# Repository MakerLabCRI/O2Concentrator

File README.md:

# O2Concentrator
# Designed by Youssouph Ndao

- Shield to connect Medical O2 sensors and valves to Movuino ESP32 for making frugal o2 O2Concentrator

- Breakout for pressure sensors

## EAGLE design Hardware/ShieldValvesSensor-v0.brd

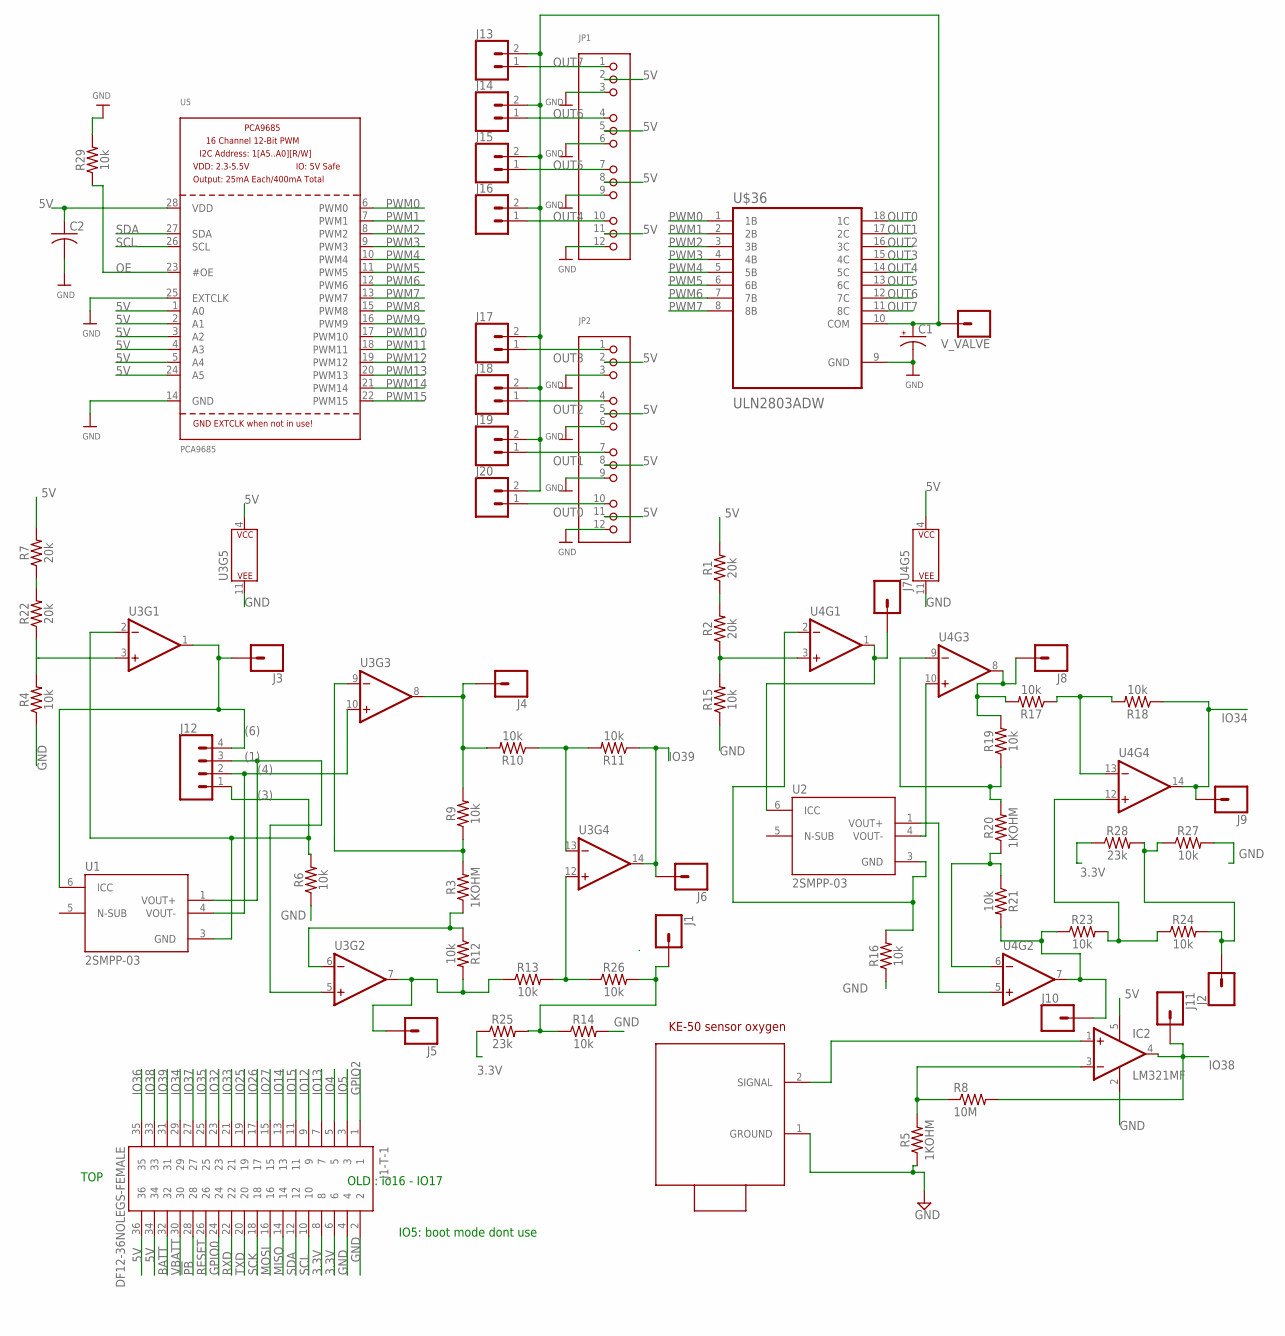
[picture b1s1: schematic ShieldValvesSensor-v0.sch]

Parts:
C1: CPOL-USE2-4; E2-4
C2: C-USC0402; C0402
IC2: LM321MF; SOT23-5
J1, J2, J3, J4, J5, J6, J7, J8, J9, J10, J11: CONN_01; 1X01
J1-T-1: DF12-36NOLEGS-FEMALE; DF12-36-DP-NL
J12: CONN_04PTH; 1X04
J13, J14, J15, J16, J17, J18, J19, J20: CONN_02; 1X02
JP1, JP2: HEADER-3X04; 3X04
R1, R2, R7, R22: 20k; 0402-TIGHT
R3, R5, R20: 1KOHM; 0402
R4, R6, R9, R10, R11, R12, R13, R14, R15, R16, R17, R18, R19, R21, R23, R24, R26, R27, R29: 10k; 0402
R8: 10M; R0402
R25, R28: 23k; 0402-TIGHT
U1, U2: 2SMPP-03; XDCR_2SMPP-03
U3, U4: LMV324SOP127P780X200-14N; SOP127P780X200-14N
U5: PCA9685; TSSOP28
U$5: KE-50; KE
U$36: ULN2803ADW; SOIC127P1030X265-18N
V_VALVE: CONN_01; 1X01

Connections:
3.3V: J1-T-1.6, J1-T-1.8, R25.1, R28.1
5V: C2.1, IC2.5 (V+), J1-T-1.34, J1-T-1.36, JP1.2, JP1.5, JP1.8, JP1.11, JP2.2, JP2.5, JP2.8, JP2.11, R1.2, R7.2, U3.4 (P$V+), U4.4 (P$V+), U5.1 (A0), U5.2 (A1), U5.3 (A2), U5.4 (A3), U5.5 (A4), U5.24 (A5), U5.28 (VDD)
!PB!: J1-T-1.28
(1): J12.3, U1.1 (VOUT+), U3.5 (+IN)
(3): J12.1, R6.2, U1.3 (GND), U3.2 (-IN)
(4): J12.2, U1.4 (VOUT-), U3.10 (+IN)
(6): J3.1, J12.4, U1.6 (ICC), U3.1 (OUT)
+IND2: R2.1, R15.2
-INA: R10.1, R11.2
-INC2: R19.1, R20.2, U4.9 (-IN)
-IND2: R16.2, U2.3 (GND), U4.2 (-IN)
BATT: J1-T-1.32
GND: C1.-, C2.2, IC2.2 (V-), J1-T-1.2, J1-T-1.4, JP1.3, JP1.6, JP1.9, JP1.12, JP2.3, JP2.6, JP2.9, JP2.12, R4.1, R5.1, R6.1, R14.2, R15.1, R16.1, R27.2, R29.2, U3.11 (P$V-), U4.11 (P$V-), U5.14 (GND), U5.25 (EXTCLK), U$5.1 (GROUND), U$36.9 (GND)
GPIO0: J1-T-1.24
GPIO2: J1-T-1.1
IO4: J1-T-1.5
IO5: J1-T-1.3
IO12: J1-T-1.9
IO13: J1-T-1.7
IO14: J1-T-1.13
IO15: J1-T-1.11
IO25: J1-T-1.19
IO26: J1-T-1.17
IO27: J1-T-1.15
IO32: J1-T-1.23
IO33: J1-T-1.21
IO34: J1-T-1.29, J9.1, R18.1, U4.14 (OUT)
IO35: J1-T-1.25
IO36: J1-T-1.35
IO37: J1-T-1.27
IO38: IC2.4 (OUT), J1-T-1.33, J11.1, R8.2
IO39: J1-T-1.31, J6.1, R11.1, U3.14 (OUT)
MISO: J1-T-1.14
MOSI: J1-T-1.16
unnamed: IC2.3 (-IN), R5.2, R8.1
unnamed: IC2.1 (+IN), U$5.2 (SIGNAL)
unnamed: R7.1, R22.2
unnamed: R1.1, R2.2
unnamed: R4.2, R22.1, U3.3 (+IN)
unnamed: R3.2, R9.1, U3.9 (-IN)
unnamed: J4.1, R9.2, R10.2, U3.8 (OUT)
unnamed: J5.1, R12.2, R13.1, U3.7 (OUT)
unnamed: R3.1, R12.1, U3.6 (-IN)
unnamed: R13.2, R26.1, U3.12 (+IN)
unnamed: J1.1, R14.1, R25.2, R26.2
unnamed: J7.1, U2.6 (ICC), U4.1 (OUT)
unnamed: U2.4 (VOUT-), U4.10 (+IN)
unnamed: R17.1, R18.2, U4.13 (-IN)
unnamed: J8.1, R17.2, R19.2, U4.8 (OUT)
unnamed: U2.1 (VOUT+), U4.5 (+IN)
unnamed: R20.1, R21.1, U4.6 (-IN)
unnamed: R23.2, R24.1, U4.12 (+IN)
unnamed: J10.1, R21.2, R23.1, U4.7 (OUT)
unnamed: J2.1, R24.2, R27.1, R28.2
OE: R29.1, U5.23 (#OE)
OUT0: J20.1, JP2.10, U$36.18 (1C)
OUT1: J19.1, JP2.7, U$36.17 (2C)
OUT2: J18.1, JP2.4, U$36.16 (3C)
OUT3: J17.1, JP2.1, U$36.15 (4C)
OUT4: J16.1, JP1.10, U$36.14 (5C)
OUT5: J15.1, JP1.7, U$36.13 (6C)
OUT6: J14.1, JP1.4, U$36.12 (7C)
OUT7: J13.1, JP1.1, U$36.11 (8C)
OUT8: C1.+, J13.2, J14.2, J15.2, J16.2, J17.2, J18.2, J19.2, J20.2, U$36.10 (COM), V_VALVE.1
PWM0: U5.6 (PWM0), U$36.1 (1B)
PWM1: U5.7 (PWM1), U$36.2 (2B)
PWM2: U5.8 (PWM2), U$36.3 (3B)
PWM3: U5.9 (PWM3), U$36.4 (4B)
PWM4: U5.10 (PWM4), U$36.5 (5B)
PWM5: U5.11 (PWM5), U$36.6 (6B)
PWM6: U5.12 (PWM6), U$36.7 (7B)
PWM7: U5.13 (PWM7), U$36.8 (8B)
PWM8: U5.15 (PWM8)
PWM9: U5.16 (PWM9)
PWM10: U5.17 (PWM10)
PWM11: U5.18 (PWM11)
PWM12: U5.19 (PWM12)
PWM13: U5.20 (PWM13)
PWM14: U5.21 (PWM14)
PWM15: U5.22 (PWM15)
RESET: J1-T-1.26
RXD: J1-T-1.22
SCK: J1-T-1.18
SCL: J1-T-1.10, U5.26 (SCL)
SDA: J1-T-1.12, U5.27 (SDA)
TXD: J1-T-1.20
VBATT: J1-T-1.30

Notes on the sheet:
TOP
OLD : io16 - IO17
IO5: boot mode dont use

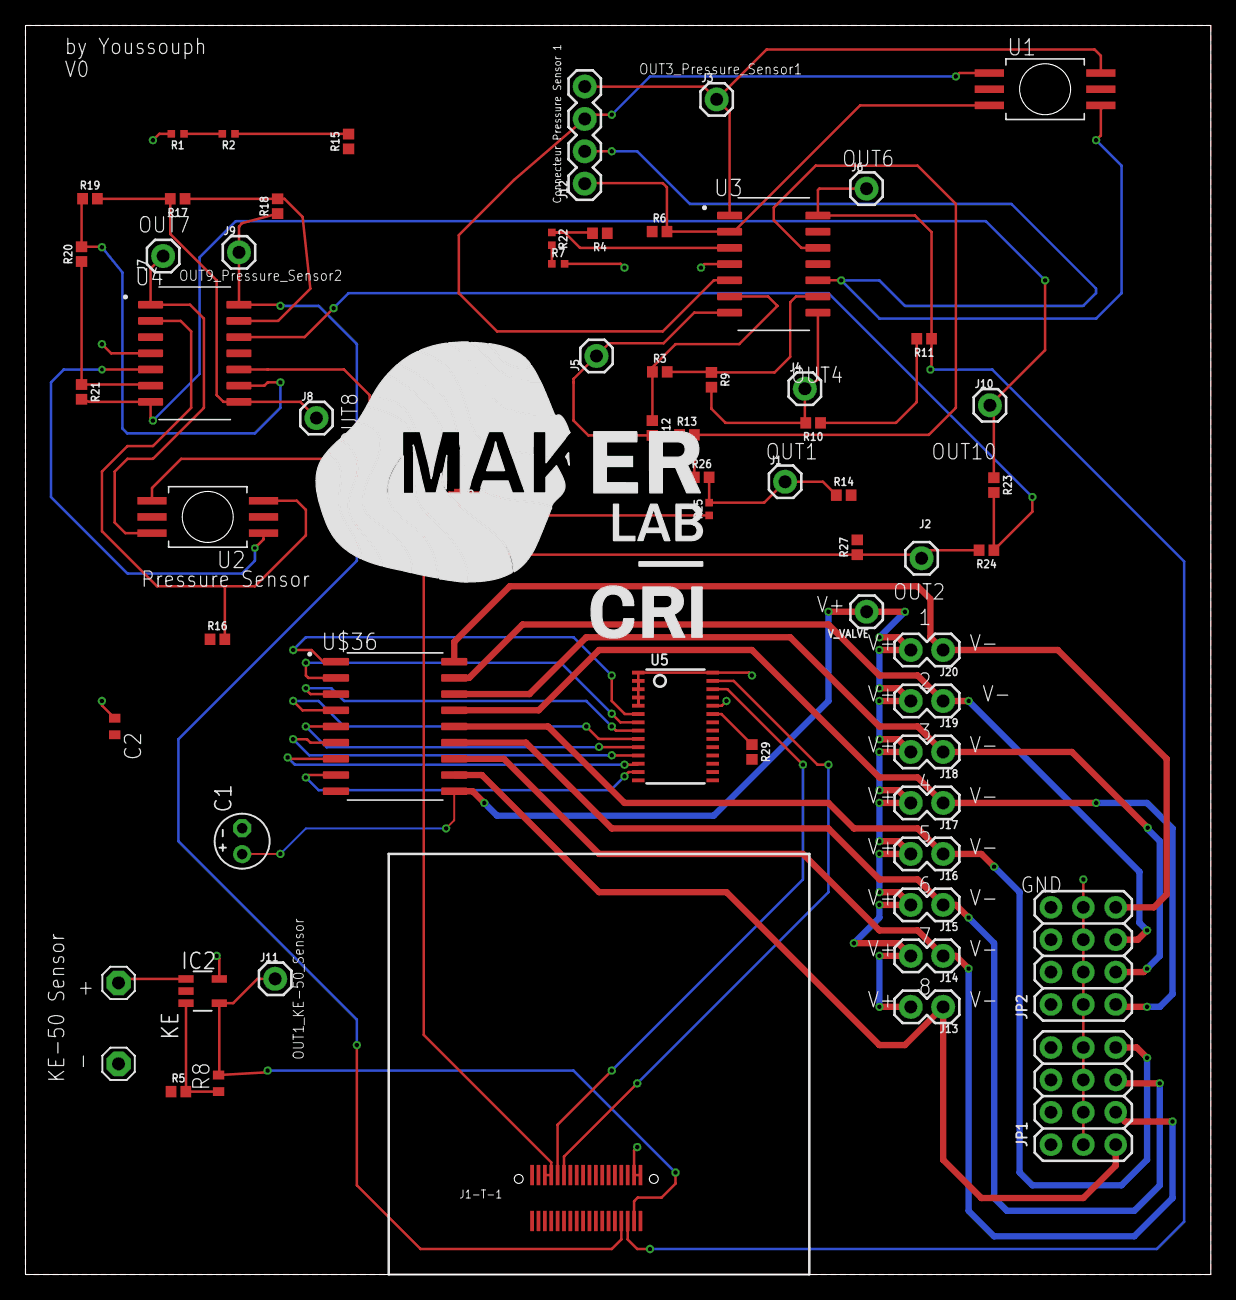
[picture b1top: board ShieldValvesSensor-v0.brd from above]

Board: 2 copper layers, 93.0 x 98.0 mm, 63 parts (0 on the bottom side), 54 nets.

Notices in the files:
parts and their libraries:
SparkFun-Resistors: Licensing: Creative Commons ShareAlike 4.0 International - https://creativecommons.org/licenses/by-sa/4.0
